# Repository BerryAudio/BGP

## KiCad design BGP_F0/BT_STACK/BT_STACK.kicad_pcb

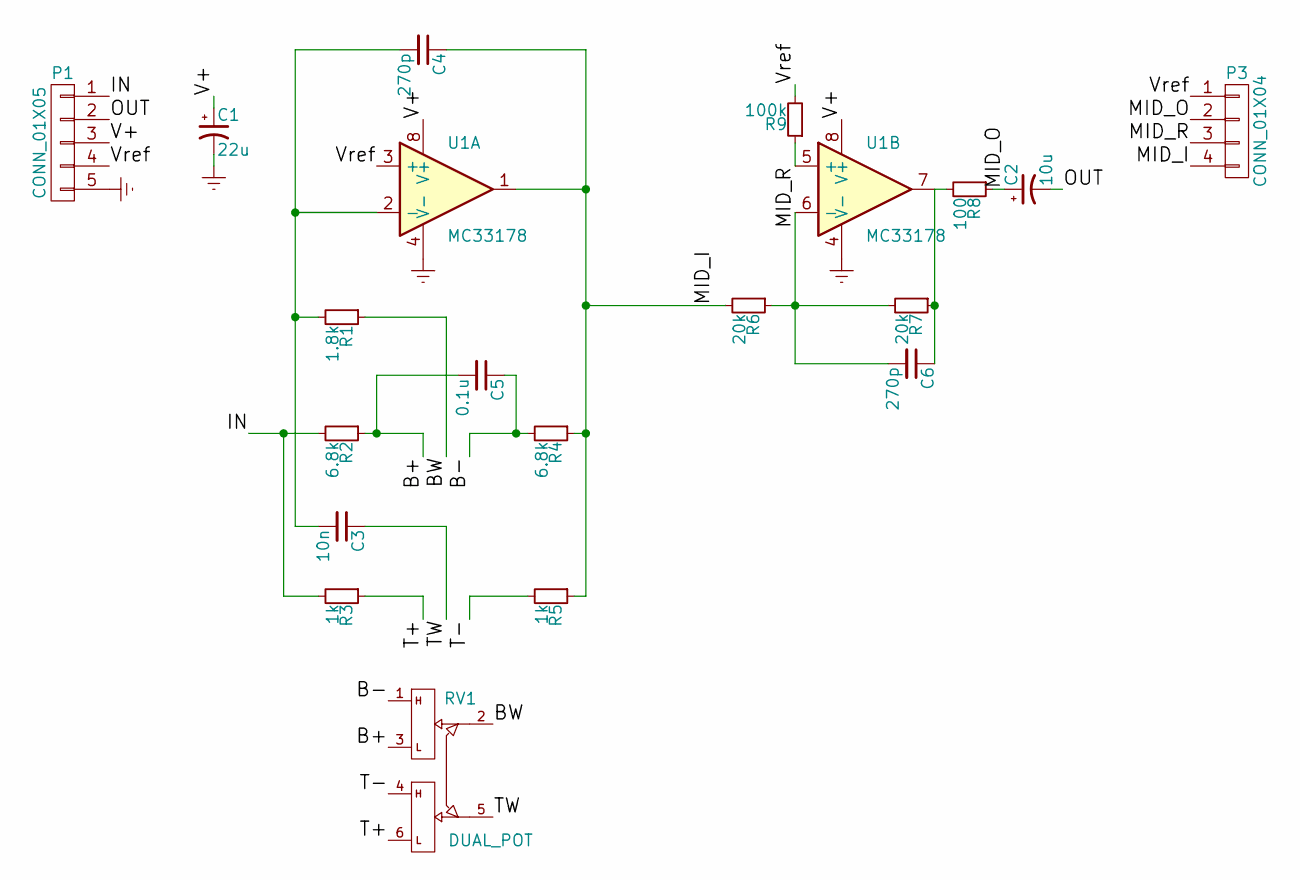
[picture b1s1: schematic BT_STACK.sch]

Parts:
C1: 22u; C_0805_HandSoldering
C2: 10u; TantalC_SizeR_EIA-2012
C3: 10n; C_0805_HandSoldering
C4, C6: 270p; C_0603
C5: 0.1u; C_0805_HandSoldering
P1: CONN_01X05; JST_PH_B5B-PH-K_05x2.00mm_Straight
P3: CONN_01X04; JST_PH_B4B-PH-K_04x2.00mm_Straight
R1: 1.8k; R_0603_HandSoldering
R2, R4: 6.8k; R_0603_HandSoldering
R3, R5: 1k; R_0603_HandSoldering
R6, R7: 20k; R_0603_HandSoldering
R8: 100; R_0603_HandSoldering
R9: 100k; R_0603_HandSoldering
RV1: DUAL_POT; Potentiometer_Alpha_Double_Vertical_Dual_Shaft
U1: MC33178; SOIC-8_3.9x4.9mm_Pitch1.27mm

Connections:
/B+: C5.2, R2.1, RV1.3
/B-: C5.1, R4.2, RV1.1
/BW: R1.1, RV1.2
/IN: P1.1, R2.2, R3.2
/MID_I: C4.1, P3.4, R4.1, R5.1, R6.2, U1.1
/MID_O: C2.1, P3.2, R8.1
/MID_R: P3.3, R9.1, U1.5 (+)
/OUT: C2.2, P1.2
/T+: R3.1, RV1.6
/T-: R5.2, RV1.4
/TW: C3.1, RV1.5
/V+: C1.1, P1.3, U1.8 (V+)
/Vref: P1.4, P3.1, R9.2, U1.3 (+)
Earth: C1.2, P1.5, U1.4 (V-)
unnamed: C3.2, C4.2, R1.2, U1.2 (-)
unnamed: C6.1, R7.1, R8.2, U1.7
unnamed: C6.2, R6.1, R7.2, U1.6 (-)

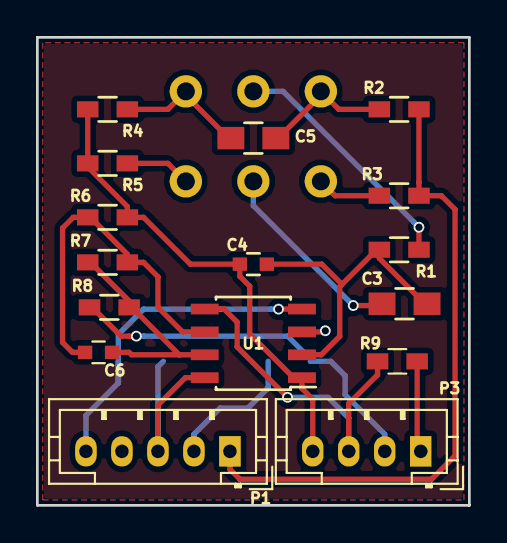
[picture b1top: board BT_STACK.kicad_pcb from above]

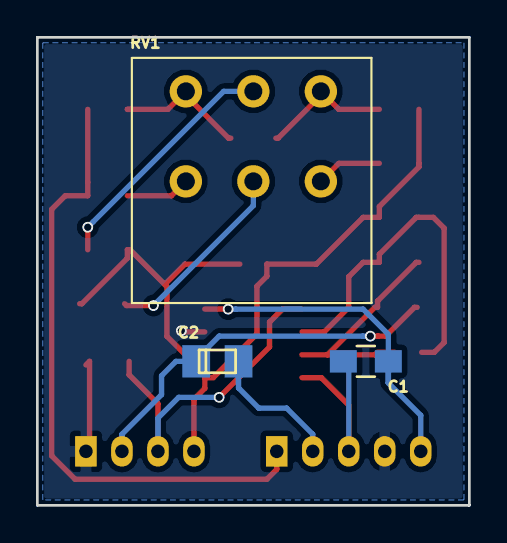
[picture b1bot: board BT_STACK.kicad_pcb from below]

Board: 2 copper layers, 24.0 x 26.0 mm, 19 parts (3 on the bottom side), 17 nets.

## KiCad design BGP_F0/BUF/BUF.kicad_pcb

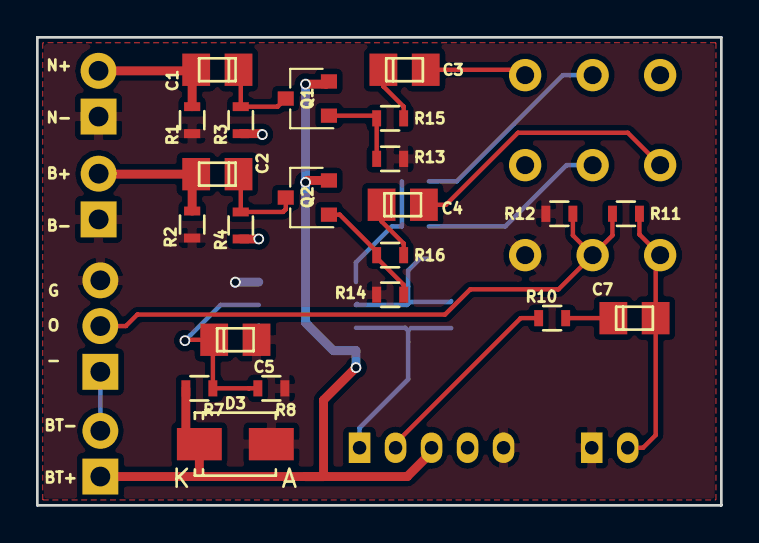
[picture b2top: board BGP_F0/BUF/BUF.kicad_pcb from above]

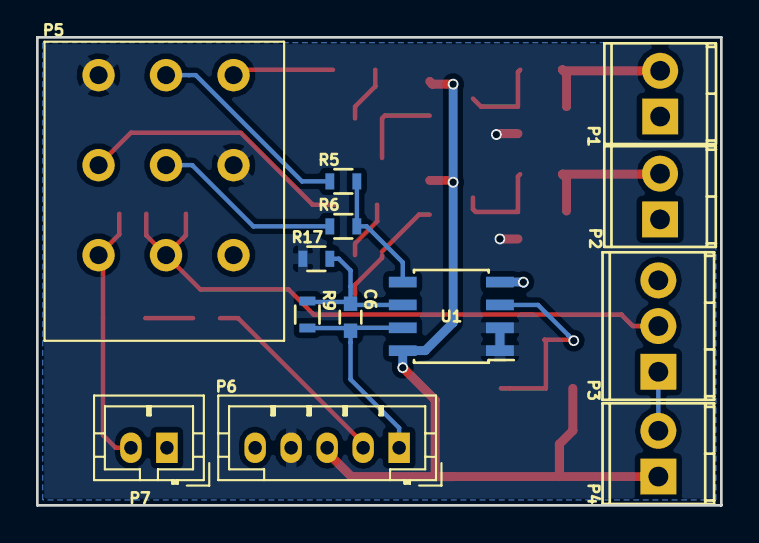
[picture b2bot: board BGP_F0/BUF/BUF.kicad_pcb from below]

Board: 2 copper layers, 38.0 x 26.0 mm, 35 parts (13 on the bottom side), 24 nets.

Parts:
C1, C2: 0.1u; TantalC_SizeR_EIA-2012
C3, C4: 1u; TantalC_SizeR_EIA-2012
C5, C7: 10u; TantalC_SizeR_EIA-2012
C6: 100p; C_0603
D3: CS1D; SMA_Standard
P1, P2, P4: CONN_01X02; TerminalBlock_Pheonix_MPT-2.54mm_2pol
P3: CONN_01X03; TerminalBlock_Pheonix_MPT-2.54mm_3pol
P5: CONN_01X09; Potentiometer_Alpha_Tripple_Vertical_Dual_Shaft
P6: CONN_01X05; JST_PH_B5B-PH-K_05x2.00mm_Straight
P7: CONN_01X02; JST_PH_B2B-PH-K_02x2.00mm_Straight
Q1, Q2: 2N5457; SC-59
R1, R2: 330k; R_0603
R3, R4: 1MEG; R_0603
R5, R6: 49.9k; R_0603
R7, R8: 100k; R_0603
R9: 15k; R_0603
R10: 100; R_0603
R11, R17: 10k; R_0603
R12: 12k; R_0603
R13, R14: 20k; R_0603
R15, R16: 1k; R_0603
U1: MC33178; SOIC-8_3.9x4.9mm_Pitch1.27mm

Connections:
/IN_B: C2.2, P2.2, R2.1
/IN_EQ: C6.1, P6.1, R9.1, U1.7
/IN_N: C1.2, P1.2, R1.1
/OUT_EQ: P6.2, R10.2
/PB1_1: C3.2, P5.1
/PB1_2: P5.2, R5.2
/PB2_2: P5.5, R6.2
/PB2_3: C4.2, P5.6
/PV_2: P3.2, P5.8, R11.2, R12.1
/PV_3: C7.2, P5.9, P7.2, R11.1
/V+: D3.1, P4.1, P6.3, Q1.2, Q2.2, R7.1, U1.8
/VRef: P5.3, P5.4, P6.4, R3.2, R4.2, R17.1, U1.1, U1.2
Earth: C5.2, D3.2, P1.1, P2.1, P3.3, P5.7, P6.5, P7.1, R1.2, R2.2, R8.2, R12.2, R13.2, R14.2, U1.4
unnamed: C1.1, Q1.3, R3.1
unnamed: C2.1, Q2.3, R4.1
unnamed: C3.1, R15.1
unnamed: C4.1, R16.1
unnamed: C5.1, R7.2, R8.1, U1.3
unnamed: C6.2, R9.2, R17.2, U1.6
unnamed: C7.1, R10.1
unnamed: P3.1, P4.2
unnamed: Q1.1, R13.1, R15.2
unnamed: Q2.1, R14.1, R16.2
unnamed: R5.1, R6.1, U1.5

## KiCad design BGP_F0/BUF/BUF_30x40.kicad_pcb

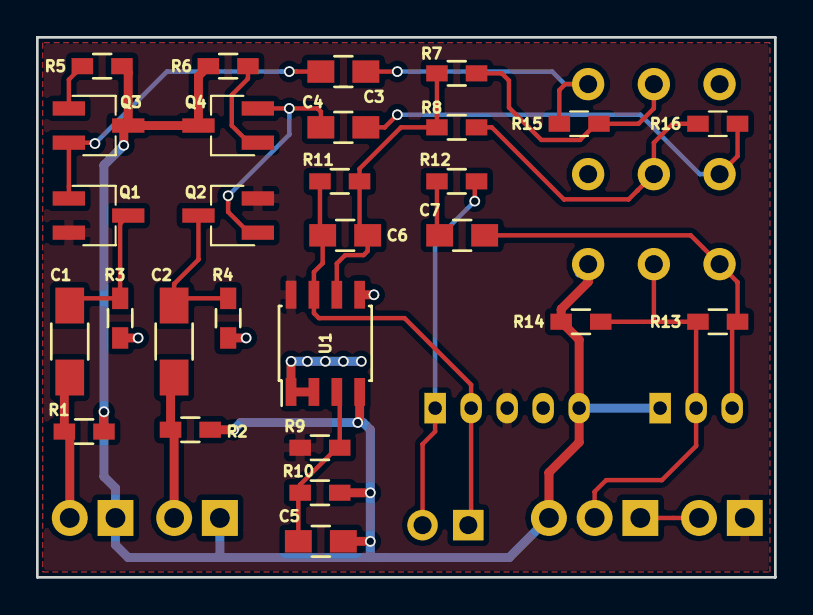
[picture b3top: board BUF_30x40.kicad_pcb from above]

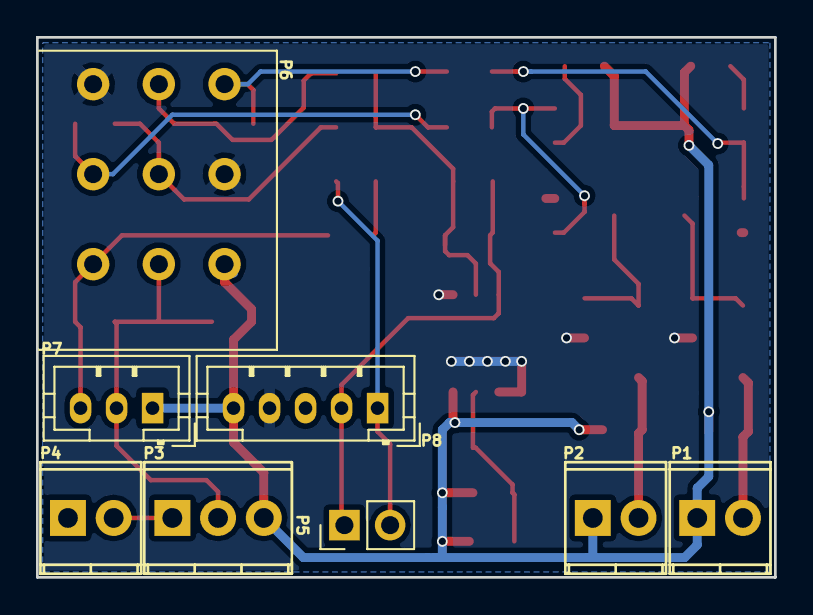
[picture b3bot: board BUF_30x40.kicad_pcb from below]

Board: 2 copper layers, 41.0 x 30.0 mm, 36 parts (8 on the bottom side), 23 nets.

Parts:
C1, C2: 0.1u; C_1206_HandSoldering
C3, C4, C5, C7: 10u; C_0805_HandSoldering
C6: 100p; C_0805_HandSoldering
P1, P2, P4: CONN_01X02; TerminalBlock_Pheonix_MPT-2.54mm_2pol
P3: CONN_01X03; TerminalBlock_Pheonix_MPT-2.54mm_3pol
P5: CONN_01X02; Pin_Header_Straight_1x02_Pitch2.54mm
P6: CONN_01X09; Potentiometer_Alpha_Tripple_Vertical_Dual_Shaft
P7: CONN_01X03; JST_PH_B3B-PH-K_03x2.00mm_Straight
P8: CONN_01X05; JST_PH_B5B-PH-K_05x2.00mm_Straight
Q1, Q2, Q3, Q4: 2SK208; SC-59_Handsoldering
R1, R2, R3, R4, R15, R16: 499k; R_0603_HandSoldering
R5, R6: 20k; R_0603_HandSoldering
R7, R8, R11: 4.99k; R_0603_HandSoldering
R9, R10: 100k; R_0603_HandSoldering
R12: 100; R_0603_HandSoldering
R13: 10k; R_0603_HandSoldering
R14: 12k; R_0603_HandSoldering
U1: MC33178; SOIC-8_3.9x4.9mm_Pitch1.27mm

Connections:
/IN_B: C1.2, P1.2, R1.1
/IN_EQ: P5.2, P8.1, R12.2
/IN_N: C2.2, P2.2, R2.1
/OUT_BUF: C6.1, P5.1, P8.2, R11.1, U1.7
/PB1_1: C3.2, P6.1, R15.2
/PB1_2: P6.2, R7.2, R15.1
/PB2_2: P6.5, R8.2, R16.1
/PB2_3: C4.2, P6.6, R16.2
/PV_2: P3.2, P6.8, P7.2, R13.2, R14.1
/PV_3: C7.2, P6.9, P7.3, R13.1
/V+: P4.1, P8.3, Q1.2, Q2.2, R9.1, U1.8
/VRef: P6.3, P6.4, P8.4, R3.2, R4.2, U1.1, U1.2, U1.5
Earth: C5.2, P1.1, P2.1, P3.3, P6.7, P7.1, P8.5, Q3.3, Q4.3, R1.2, R2.2, R5.2, R6.2, R10.2, R14.2, U1.4
unnamed: C1.1, Q1.3, R3.1
unnamed: C2.1, Q2.3, R4.1
unnamed: C3.1, Q1.1, Q3.2
unnamed: C4.1, Q2.1, Q4.2
unnamed: C5.1, R9.2, R10.1, U1.3
unnamed: C6.2, R7.1, R8.1, R11.2, U1.6
unnamed: C7.1, R12.1
unnamed: P3.1, P4.2
unnamed: Q3.1, R5.1
unnamed: Q4.1, R6.1

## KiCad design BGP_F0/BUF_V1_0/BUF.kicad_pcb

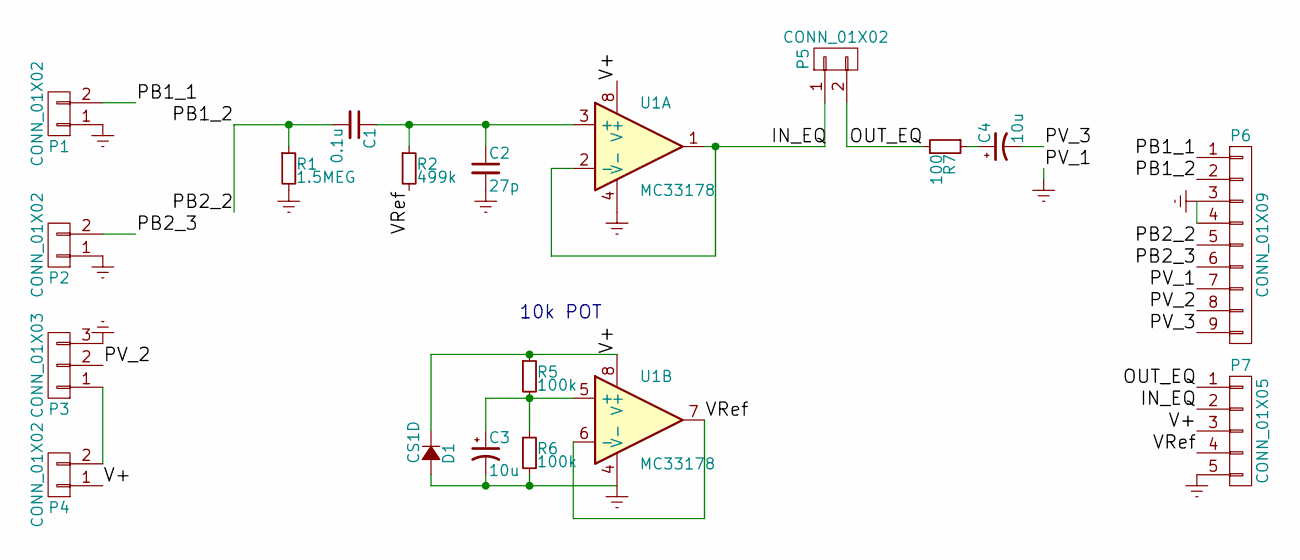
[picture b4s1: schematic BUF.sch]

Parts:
C1: 0.1u; TantalC_SizeR_EIA-2012
C2: 27p; C_0603_HandSoldering
C3, C4: 10u; TantalC_SizeR_EIA-2012
D1: CS1D; SMA_Standard
P1, P2, P4: CONN_01X02; TerminalBlock_Pheonix_MPT-2.54mm_2pol
P3: CONN_01X03; TerminalBlock_Pheonix_MPT-2.54mm_3pol
P5: CONN_01X02; JST_PH_B2B-PH-K_02x2.00mm_Straight
P6: CONN_01X09; Potentiometer_Alpha_Tripple_Vertical_Dual_Shaft
P7: CONN_01X05; JST_PH_B5B-PH-K_05x2.00mm_Straight
R1: 1.5MEG; R_0603
R2: 499k; R_0603
R5, R6: 100k; R_0603
R7: 100; R_0603
U1: MC33178; SOIC-8_3.9x4.9mm_Pitch1.27mm

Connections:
/IN_EQ: P5.1, P7.2, U1.1, U1.2 (-)
/OUT_EQ: P5.2, P7.1, R7.2
/PB1_1: P1.2, P6.1
/PB1_2: C1.2, P6.2, P6.5, R1.1
/PB2_3: P2.2, P6.6
/PV_2: P3.2, P6.8
/PV_3: C4.2, P6.9
/V+: D1.1 (K), P4.1, P7.3, R5.1, U1.8 (V+)
/VRef: P7.4, R2.2, U1.6 (-), U1.7; also elsewhere on the board
Earth: C2.2, C3.2, D1.2 (A), P1.1, P2.1, P3.3, P6.3, P6.4, P6.7, P7.5, R1.2, R6.2, U1.4 (V-)
unnamed: C1.1, C2.1, R2.1, U1.3 (+)
unnamed: C3.1, R5.2, R6.1, U1.5 (+)
unnamed: C4.1, R7.1
unnamed: P3.1, P4.2

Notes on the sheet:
10k POT

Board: 2 copper layers, 19 parts (7 on the bottom side), 14 nets, no tracks yet.

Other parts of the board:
R4: 4.99k; R_0603

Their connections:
/VRef: R4.2; also elsewhere on the board

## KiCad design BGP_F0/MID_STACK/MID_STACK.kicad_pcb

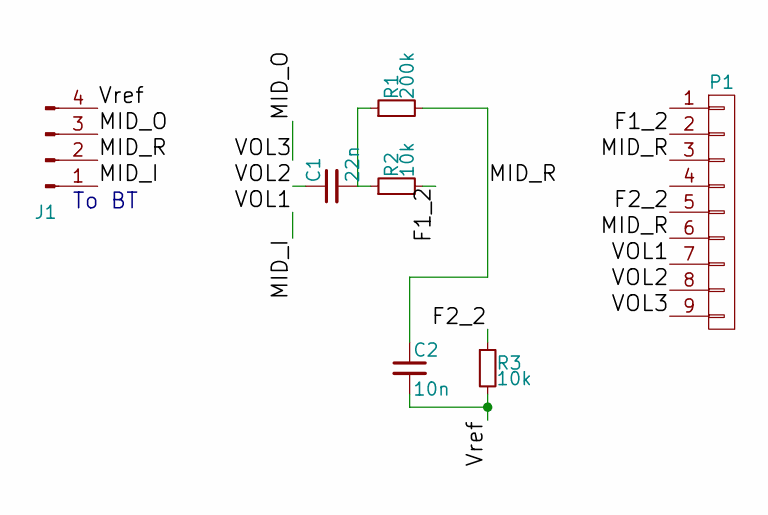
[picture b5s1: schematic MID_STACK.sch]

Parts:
C1: 22n; C_1206
C2: 10n; C_0805
J1: Conn_01x04_Male; Pin_Header_Straight_1x04
P1: CONN_01X09; Potentiometer_Alpha_Tripple_Vertical_Dual_Shaft
R1: 200k; R_0603_HandSoldering
R2, R3: 10k; R_0603_HandSoldering

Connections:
/F1_2: P1.2, R2.2
/F2_2: P1.5, R3.1
/MID_I: J1.1, P1.7
/MID_O: J1.3, P1.9
/MID_R: C2.1, J1.2, P1.3, P1.6, R1.2
/VOL2: C1.1, P1.8
/Vref: C2.2, J1.4, R3.2
unnamed: C1.2, R1.1, R2.1

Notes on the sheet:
To BT

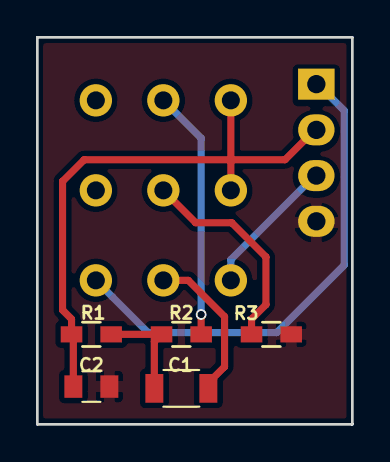
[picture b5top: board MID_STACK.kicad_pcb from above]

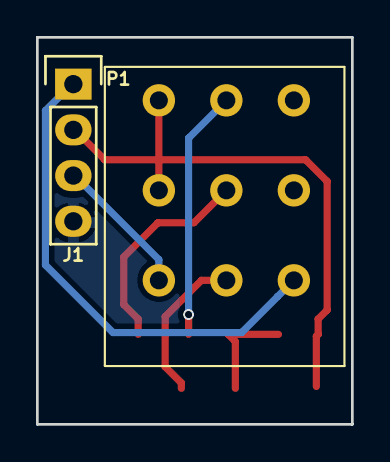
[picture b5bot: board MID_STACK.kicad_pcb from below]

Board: 2 copper layers, 17.5 x 21.5 mm, 7 parts (2 on the bottom side), 8 nets.

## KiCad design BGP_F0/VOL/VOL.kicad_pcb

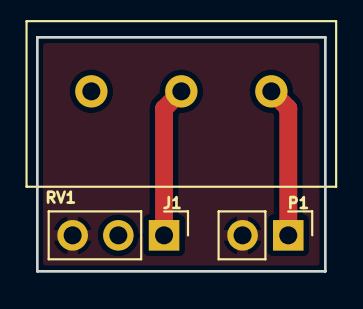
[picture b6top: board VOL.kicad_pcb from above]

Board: 2 copper layers, 16.0 x 13.0 mm, 3 parts (0 on the bottom side), 3 nets.

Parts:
J1: Conn_01x03_Female; Pin_Header_Straight_1x03_Pitch2.54mm
P1: CONN_01X02; Pin_Header_Straight_1x02_Pitch2.54mm
RV1: POT; Potentiometer_Alpha_RV16

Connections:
/VOL_1: P1.1, RV1.1
/VOL_3: J1.3, P1.2
unnamed: J1.1, RV1.2
